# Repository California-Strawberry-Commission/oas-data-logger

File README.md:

# Operator Aid Systems Data Collection

## Objective

A common, fast and reliable method for data collection for Operator Aid Systems, such as bug vac and spray rig.

We continuously gather data from connected sensors, and save it to an SD card. When connected to WiFi, the data is uploaded to a server. We provide a web-based interface to visualize the data.

## Hardware

### v0

The [Adafruit ItsyBitsy ESP32](https://learn.adafruit.com/adafruit-itsybitsy-esp32/overview) was ultimately selected due to its small form factor, relatively large number of GPIO pins, power management, Wi-Fi and Bluetooth capabilities, and I2C connector. We had originally worked with the Sparkfun Thing Plus. However, the ItsyBitsy has a smaller size, extra power management features, and better isolation between the VCC and battery rails. With the Sparkfun Thing Plus, we needed to mod in a better diode onto the board to get USB power detection to work, and found that GPS did not work on I2C (and thus had to use UART).

Relevant features include:

- USB to serial converter chip
- Power regulator
- STEMMA QT I2C connector (which we use for the GPS module)
- Low power (light sleep at 4mA, deep sleep at ~10uA)
- Wi-Fi and Bluetooth
- 20 GPIO pins
- SPI pins (which we use for the MicroSD module)
- User switch
- Small form factor

The GPS module provides support for GPS, GLONASS, GALILEO, and QZSS, providing updates at up to 10 Hz and with both UART and I2C interfaces.

### v1

See https://github.com/California-Strawberry-Commission/oas-data-logger-hardware

## Software

### ESP32

`oas-logger` is a PlatformIO (IDE for embedded systems, based on VSCode) project for the ESP32 to log data from various attached sensors (currently only GPS) using the Arduino API. It depends on `dlflib`, which is used for writing and uploading log data.

### Server

`data-visualizer` is a Next.js app deployed on Vercel for uploading and visualizing OAS data. It depends on `dlflib-js`, which is used for parsing `.dlf` files, and so we use an npm workspace.

See [README.md](software/data-visualizer/README.md).

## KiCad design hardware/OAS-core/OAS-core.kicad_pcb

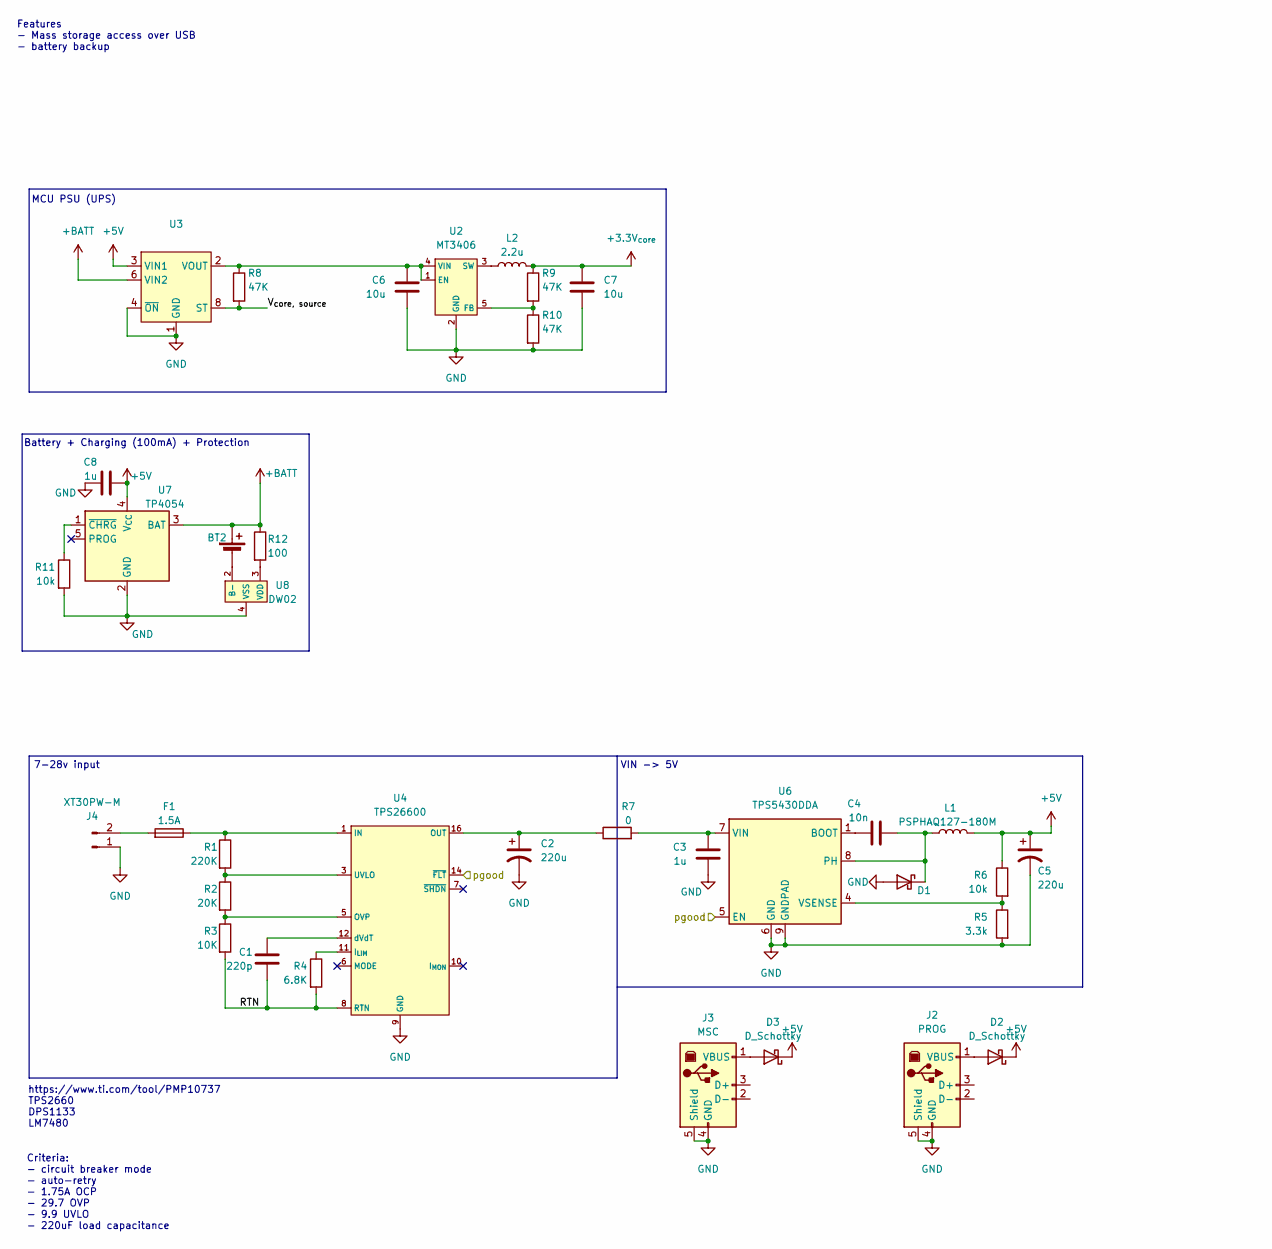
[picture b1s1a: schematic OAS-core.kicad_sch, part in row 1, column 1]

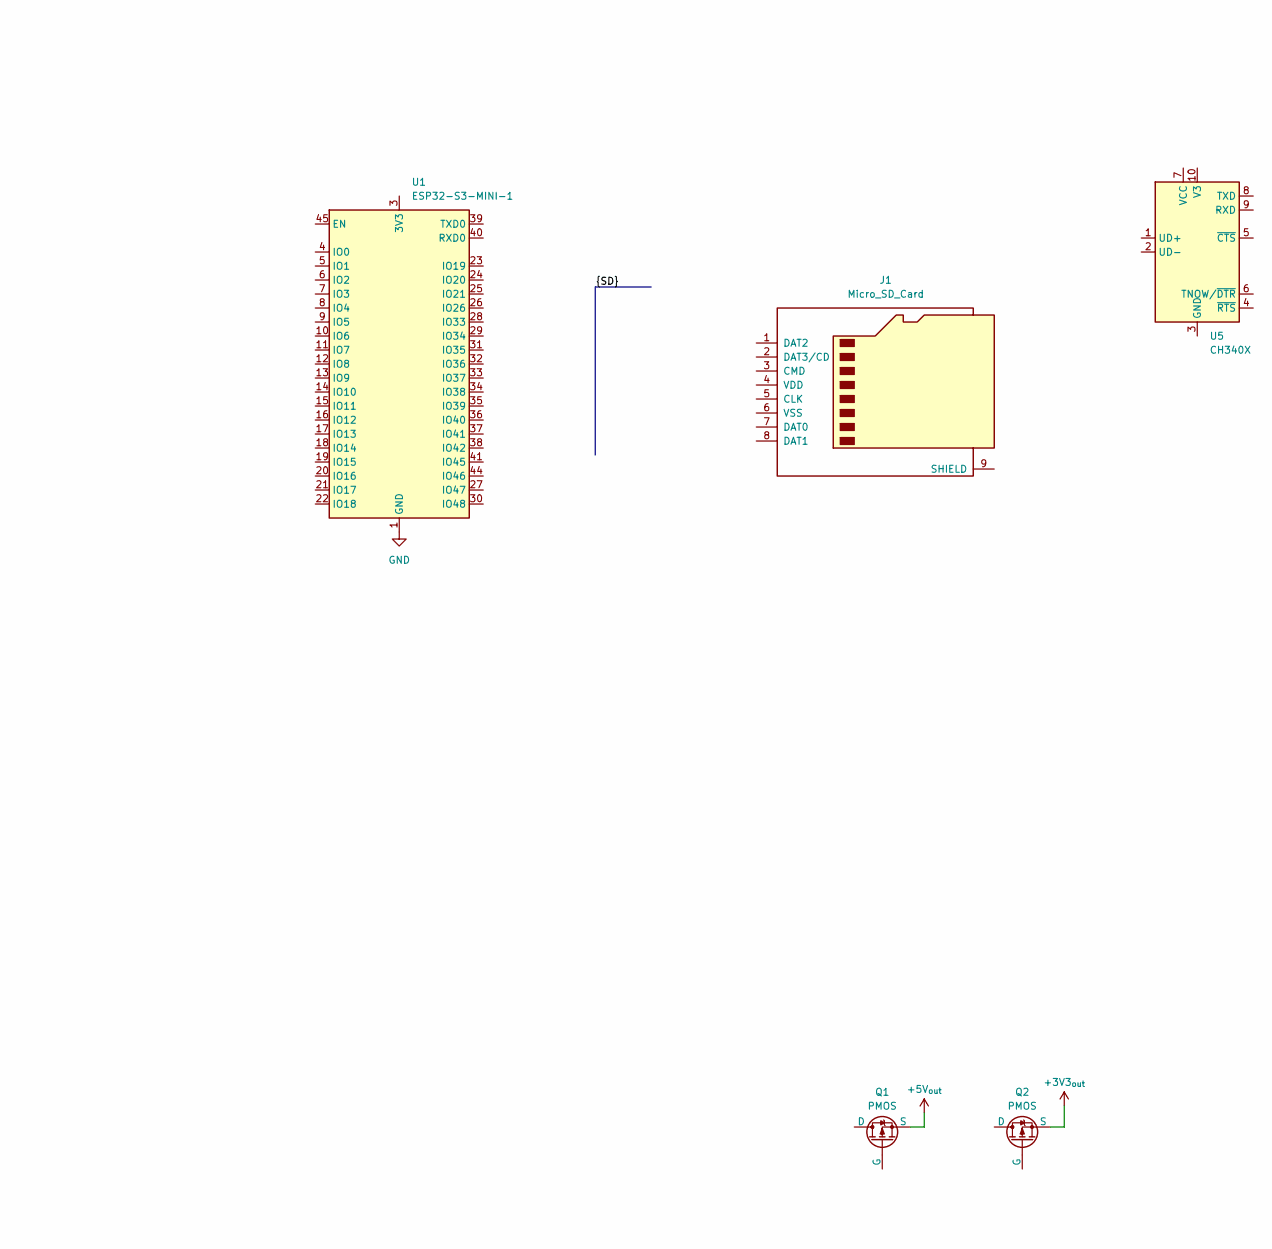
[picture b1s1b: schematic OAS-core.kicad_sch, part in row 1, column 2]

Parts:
BT2: Battery_Cell; JST_PH_B2B-PH-SM4-TB_1x02-1MP_P2.00mm_Vertical
C1: 220p; C_0402_1005Metric
C2: 220u; CP_Elec_8x10.5; LCSC C2983323
C3, C8: 1u; C_0402_1005Metric
C4: 10n; C_0402_1005Metric
C5: 220u; CP_Elec_6.3x5.9; LCSC C2939793
C6, C7: 10u; C_0805_2012Metric; LCSC C15850
D1: D_Schottky; D_SMA; LCSC C7420369
D2, D3: D_Schottky
F1: 1.5A; R_0603_1608Metric; LCSC C2924957
J1: Micro_SD_Card; microSD_HC_Hirose_DM3AT-SF-PEJM5; LCSC C114218
J2: PROG; USB_B_OST_USB-B1HSxx_Horizontal
J3: MSC; USB_B_OST_USB-B1HSxx_Horizontal
J4: XT30PW-M; AMASS_XT30PW-M_1x02_P2.50mm_Horizontal
L1: PSPHAQ127-180M; L_12x12mm_H8mm; LCSC C2983064
L2: 2.2u; L_1008_2520Metric; LCSC C5156791
Q1, Q2: PMOS
R1: 220K; R_0402_1005Metric
R2: 20K; R_0402_1005Metric
R3: 10K; R_0402_1005Metric
R4: 6.8K; R_0402_1005Metric
R5: 3.3k; R_0402_1005Metric; LCSC C25890
R6, R11: 10k; R_0402_1005Metric
R7: 0; R_0402_1005Metric
R8, R9, R10: 47K; R_0402_1005Metric
R12: 100; R_0402_1005Metric
U1: ESP32-S3-MINI-1; ESP32-S2-MINI-1
U2: MT3406; SOT-23-5; LCSC C89358
U3: LM66200; SOT-583-8
U4: TPS26600; HTSSOP-16-1EP_4.4x5mm_P0.65mm_EP3.4x5mm_Mask2.46x2.31mm_The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
U5: CH340X; MSOP-10_3x3mm_P0.5mm
U6: TPS5430DDA; TI_SO-PowerPAD-8_ThermalVias; LCSC C9864
U7: TP4054; TSOT-23-5; LCSC C32574
U8: DW02; SOT-23-5; LCSC C7420470

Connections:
+3.3V_{core}: C7.1, L2.2, R9.1
+5V: C5.1, C8.1, D2.1 (K), D3.1 (K), L1.2, R6.1, U3.3 (VIN1), U7.4 (V_{CC})
+BATT: BT2.1 (+), R12.1, U3.6 (VIN2), U7.3 (BAT)
/RTN: C1.2, R3.2, R4.2, U4.8 (RTN), U4.17 (PAD)
/V_{core, source}: R8.2, U3.8 (ST)
/pgood: U4.14 (~FLT), U6.5 (EN)
GND: C2.2, C3.2, C5.2, C6.2, C7.2, C8.2, D1.2 (A), J2.4 (GND), J2.5 (Shield), J3.4 (GND), J3.5 (Shield), J4.1, R5.2, R10.2, R11.2, U1.1 (GND), U1.2 (GND), U1.42 (GND), U1.43 (GND), U1.46 (GND), U1.47 (GND), U1.48 (GND), U1.49 (GND), U1.50 (GND), U1.51 (GND), U1.52 (GND), U1.53 (GND), U1.54 (GND), U1.55 (GND), U1.56 (GND), U1.57 (GND), U1.58 (GND), U1.59 (GND), U1.60 (GND), U1.61 (GND), U1.62 (GND), U1.63 (GND), U1.64 (GND), U1.65 (GND), U2.2 (GND), U3.1 (GND), U3.4 (~ON), U3.5 (GND), U4.9 (GND), U6.6 (GND), U6.9 (GNDPAD), U7.2 (GND), U8.4 (VSS), U8.5 (VSS)
unnamed: BT2.2 (-), U8.2 (B-)
unnamed: C2.1, R7.1, U4.15 (OUT), U4.16 (OUT)
unnamed: C4.2, D1.1 (K), L1.1, U6.8 (PH)
unnamed: D2.2 (A), J2.1 (VBUS)
unnamed: D3.2 (A), J3.1 (VBUS)
unnamed: F1.1, R1.1, U4.1 (IN), U4.2 (IN)
unnamed: F1.2, J4.2
unnamed: C6.1, R8.1, U2.1 (EN), U2.4 (VIN), U3.2 (VOUT), U3.7 (VOUT)
unnamed: R9.2, R10.1, U2.5 (FB)
unnamed: L2.1, U2.3 (SW)
unnamed: R4.1, U4.11 (I_{LIM})
unnamed: R2.2, R3.1, U4.5 (OVP)
unnamed: R1.2, R2.1, U4.3 (UVLO)
unnamed: C1.1, U4.12 (dVdT)
unnamed: C4.1, U6.1 (BOOT)
unnamed: C3.1, R7.2, U6.7 (VIN)
unnamed: R5.1, R6.2, U6.4 (VSENSE)
unnamed: R11.1, U7.1 (~CHRG)
unnamed: R12.2, U8.3 (VDD)

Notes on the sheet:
VIN -> 5V
Criteria: - circuit breaker mode - auto-retry - 1.75A OCP - 29.7 OVP - 9.9 UVLO - 220uF load capacitance
Battery + Charging (100mA) + Protection
https://www.ti.com/tool/PMP10737 TPS2660 DPS1133 LM7480
7-28v input
MCU PSU (UPS)
Features - Mass storage access over USB - battery backup

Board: 2 copper layers, 37 parts (0 on the bottom side), 24 nets, no tracks yet.

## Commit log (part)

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2026-01-16 [dlflib] s/CSCLogger/DLFLogger
2026-01-20 [oas-logger] Modify app_v0 to check for firmware updates
2026-01-20 [oas-logger] Modify v0 and v1 apps to check for firmware updates (#83)
    * [oas-logger] Modify app_v0 to check for firmware updates
    * [oas-logger] Modify app_v1 to check for firmware updates
2026-01-20 [dlflib] Made necessary changes to decouple dlflib from deviceauth and main.
2026-01-20 Package-lock.json updated
2026-01-20 Revert platformio.ini to main state
2026-01-20 [oas-logger] Changed Serial.println(s) to new logger standard, disabled serial logging until after provisioning state.
2026-01-21 [data-viz] Implement device filter (#85)
2026-01-22 Refactored provision-device.js to be more in line with publish-firmware.mjs
2026-01-22 DeviceAuth revised to use constexpr, a namespace, .c_str() fix, and check hex properly.
2026-01-22 Modified request_signer to use const String& and pass deviceId and secret into the constructor.
2026-01-22 chore: revert platformio.ini changed by VSCode.
2026-01-22 End-to-End Device Authentication & Secure Provisioning (#74)
    * [data-visualizer] API created to facilitate secret encryption for server side.
    * [data-visualizer][prisma] Modify DB schema to support authentication of devices for upload.
    * [data-visualizer] Implement secure device provisioning and HMAC verification JS side.
    * [dlflib] Add authentication headers.
    * [oas-logger] Implement device-side provisioning and authentication.
    * [data-visualizer] Update package.json for serialport and axios under devDependencies.
2026-01-23 [provision] Fix import
2026-01-23 [oas-logger][v1-app] Fix garbled IP log
2026-01-23 [oas-logger] Fix WiFi connection on boot
2026-01-26 [oas-logger] Fix WiFi connection on boot (#93)
    * [oas-logger] Fix WiFi connection on boot
    * [oas-logger] Fixed v1-app compile
2026-01-26 [oas-logger] Add clear log line on boot
2026-01-26 [oas-logger] Tweak order of delay during boot (#97)
2026-01-27 [data-viz] Add provisioned status to Devices list in Admin Portal (#100)
2026-01-27 [data-viz] Make Combobox and selector components controlled and add delete run button to main page
2026-01-28 [oas-logger] Add heap monitor
2026-01-28 [oas-logger] Add heap monitor (#104)
    * [oas-logger] Add heap monitor
    * [oas-logger] Add test flag to app_v0 and app_v1 to log heap usage
2026-01-29 [dlflib] Increased Flusher task stack size.
2026-01-29 [dlflib] Modified comment to address new stack size.
2026-01-30 [ezlog][trivial] Organize static state vars
2026-01-30 [oas-logger] Switch to EzLog
2026-02-02 [data-viz] Add error details to console log for verifyDeviceSignature (#110)
2026-02-02 [oas-logger][ezlog] Add core, task, filename, line, function name to log lines (#111)
2026-02-02 Implement solution to WiFi reconnection never being attempted. (#106)
    * [dlflib] Increased Flusher task stack size.
    * [oas-logger] Implement solution for reconnecting to WiFi when out of range.
    * [dlflib] Modified comment to address new stack size.
    * [oas-logger] Modified Polling Loop comment to be more accurate.
2026-02-04 [data-viz][auth] Add dev bypass for provisioned device auth endpoints
2026-02-04 [data-viz][auth] Add dev bypass for user auth endpoints
2026-02-04 [data-viz] Secure firmware endpoint for provisioned devices only
2026-02-06 [data-viz] Increase dwell radius (#117)
2026-02-11 [data-viz] Revamp UI
2026-02-11 [data-viz] Complete UI revamp (#118)
    * [data-viz] Add top app bar
    * [data-viz] Revamp UI
    * [data-viz] Add logo
    * [data-viz] Responsive UI for mobile
2026-02-11 [data-viz] Loading states in data selector (#120)
2026-02-19 [data-viz] Sync selected timestamp between map and speed chart, and improve performance of rerenders
2026-02-23 [data-viz] Update Prisma to v7 (#125)
2026-02-25 [dlflib] Remove unnecessary type aliases
2026-02-25 [oas-logger][v0] Delete GPS task on sleep
2026-02-27 [dlflib][UploaderComponent] Change connectToEndpoint to just create a unique_ptr of WifiClient to begin with
2026-02-27 [dlflib][UploaderComponent] Close all file handles
2026-03-02 [dlflib][UploaderComponent] Add RetentionMode to options
2026-03-02 [dlflib][UploaderComponent] Avoid heap fragmentation (#127)
    * [dlflib][UploaderComponent] Change connectToEndpoint to just create a unique_ptr of WifiClient to begin with
    * [dlflib][UploaderComponent] Remove unnecessary CRLF from request header
    * [dlflib][UploaderComponent] Close all file handles
    * [dlflib][UploaderComponent] Reuse WiFiClient to avoid heap fragmentation
    * [dlflib] Eliminate usage of String in UploaderComponent
    * [dlflib][UploaderComponent] Add RetentionMode to options
2026-03-02 [dlflib] Eliminate String everywhere except RequestSigner (#128)
    * [dlflib] Eliminate String from AbstractStream and DLFLogger::prune
    * [dlflib] Eliminate String everywhere except RequestSigner
2026-03-03 [PR #129] Requested changes made.
2026-03-03 [data-viz] Implement multiple run visualization
2026-03-05 [data-viz] Add matching color coding to data selector and visualization
2026-03-05 [data-viz] Add comparison limit
2026-03-05 [data-viz] Tweak speed chart tooltip (#132)
2026-03-05 [oas-logger] Remove unused GPS_BAUD_RATE (#133)
2026-03-05 [data-viz] Fix current position marker color (#134)
2026-03-10 [oas-logger] Change DeviceAuth public API to use c-strings and moved logic from main into DeviceAuth that handles provision and reboot sequence. (#136)
    * [oas-logger] Change DeviceAuth public API to use c-strings and moved logic from main into DeviceAuth that handles provision and reboot sequence.
    * [oas-logger][deviceAuth] secretLen to secretBufferLen, comment for minimum size buffer, lastPrint moved to outside loop.
2026-03-10 [oas-logger] Avoid String heap allocs in OtaUpdater
2026-03-11 [data-viz] Make TimeSeriesChart generic (#142)
2026-03-12 [data-viz] Add dwell time chart (#143)
2026-03-13 [data-viz] Sync run selections to URL (#144)
2026-03-18 [data-viz] Remove unnecessary ResponsiveContainer
2026-03-18 [data-viz] When zoomed, adjust Y domain to fit visible data
2026-03-18 [data-viz] Add posthog events
2026-03-18 [data-viz] Integrate product analytics pipeline with PostHog (#149)
    * [data-viz] Integrate PostHog
    * [data-viz] Add posthog events
    * [data-viz] Add posthog identification on page render
2026-03-20 [oas-logger][dlflib] Task sizes decreased to 2560 words based on stack audit. (#150)
2026-03-23 [data-viz] Adjust point downsampling to chart zoom region
2026-03-23 [oas-logger] Enable OTA updates
2026-03-23 [data-viz] Add share button (#155)
2026-03-24 [data-viz] Remove RunData from prisma schema
2026-03-24 [oas-logger] In depth audit of sleep_monitor, increase stack size accordingly (#160)
2026-03-25 [data-viz] Add retries for S3 upload (#164)
2026-03-25 [data-viz] Fix deleting a run to clear run cache (#165)
2026-03-25 [oas-logger] On upload check for any 2XX status
2026-03-25 [data-viz] Fix map recentering when switching between runs
2026-03-30 [dlflib] Move device secret to UploaderComponent Options (#172)
2026-03-30 [oas-logger] Use root CA cert for uploader (#173)
2026-03-30 [oas-logger] Use root CA cert for OTA update (#174)
2026-04-06 [dlflib] Implement chunked uploads (#176)
    * [dlflib] Implement chunked uploads
    * [dlflib][upload] Use chunked upload path for partial uploads
2026-04-07 [oas-logger] Improve sleep button logic to make it feel more responsive (#177)
2026-04-09 [dlflib] Add checks for FreeRTOS resource creation and fix potential stream buffer overrun (#178)
    * [dlflib] Add checks for all FreeRTOS resource creation
    * [dlflib] Fix potential stream buffer overrun when there are many event streams
2026-04-09 [oas-logger] Ensure state machine state is thread safe
2026-04-10 [data-viz] API route param validation
2026-04-10 [data-viz][trivial] Update README example request to reflect valid UUID requirement (#181)
2026-04-13 [data-viz] Extract api route auth logic to a handler wrapper (#182)
2026-04-13 [data-viz] Add unit tests for data-visualizer (#183)
    * [data-viz] Add scaffolding for vitest unit tests
    * [data-viz] Add unit tests for lib
2026-04-15 Add test script to root package.json
2026-04-15 Add test github workflow
2026-04-15 Add Github Action for building firmware (#186)
2026-04-15 [dlflib-js][encoder] Modified comments, moved float implementation to construct_floats.ts.
2026-04-15 Rename test workflow to server
2026-04-15 [dlflib-js][package.json] Add construct-js and ieee754 dependencies.
2026-04-16 [dlflib-js] Clean up config files (#188)
2026-04-17 Bump dependency versions to address security alerts
2026-04-17 [oas-logger] Log WiFi RSSI
2026-04-17 [dlflib-js][construct_float] Comment created acknowledging source code origins.
2026-04-17 [software] Update package-lock.json for npm installs.
2026-04-21 [data-viz] Add map overlay for wifi RSSI (#192)
2026-04-22 [data-viz] Only show wifi rssi overlay if there exists wifi data
2026-04-23 [data-viz] Modify combobox to scroll to the selected element when expanded
2026-04-23 [data-viz] Add run summary
2026-04-24 [data-viz] Move GPS data processing functions into separate functions and add unit tests
2026-04-24 [data-viz] Move GPS data processing functions into separate functions and add unit tests for gps viz (#197)
    * [data-viz] Move GPS data processing functions into separate functions and add unit tests
    * [data-viz] Add unit tests for time-series-chart
2026-04-28 [dlflib-js][dlflib.ts] Removed unused import NullTerminatedStringType.
2026-04-29 [dlflib] Update README
2026-04-29 [dlflib-js][dlflib.ts] Match offset to _____offset, utilize create_parser logic to handle non-primitive in polled_data.
2026-04-30 [dlflib-js][dlflib.ts] Addressed PR comments.
2026-05-04 [dlflib-js][dlflib.ts] Passed size to getEncoderField.
2026-05-07 [data-viz] Fix import in gps-processing.test.ts
2026-05-08 [data-viz] Implement GPS data visualization for Day view mode
2026-05-08 [dlflib-js] Rename types, variables, methods to improve clarity and consistency
2026-05-08 New commit
2026-05-08 [dlflib-js] Additional typing (#203)
2026-05-11 [data-viz] Add ability to select and visualize data by session (#206)
    * [data-viz] Swap Run and Day selector positions
    * [data-viz] Add ability to select and visualize data by session
2026-05-11 [data-viz] For map and charts in session view, ensure we don't connect points across different runs (#207)
2026-05-11 [data-viz] Add missing dwellMinsSeries dep when memoizing sessionSummaries
2026-05-11 [data-viz] Fix session view URL handling
2026-05-11 [oas-logger][DeviceAuth] Added provisioning helpers for duplicated logic, added functionality for pulling secret from already provisioned device, moved unnecessarily public functions to private.
2026-05-11 [oas-logger][DeviceAuth] Match variable used to parameter name after changing for readability.
2026-05-12 [oas-logger] Attempt wifi reconnect during RUNNING state and turn on partial uploads (#214)
2026-05-12 [data-viz] Add Live indicator to summary cards (#215)
    * [data-viz] Fix active indicator when selecting a session
    * [data-viz] Add Live indicator to summary cards
2026-05-14 Trialed a few approaches for reliability, picked cleanest one which aligned with your suggestion.
2026-05-14 [oas-logger][app_v1][rev2] Pin changes and LED for rev2.
2026-06-01 [dlflib] Fix bug where calling LogFile::flush will corrupt the logfile
2026-06-01 Hard migration to new board specs, Genki will run v0.
2026-06-02 [dlflib][partial uploads] Don't finalize on chunk upload (#220)
    * [dlflib] Add chunkUploadTimeoutMs to options
    * [dlflib][partial uploads] Don't finalize on chunk upload
2026-06-02 [data-viz] When visualizing active run or session, automatically refetch data (#222)
2026-06-02 [oas-logger][rev2] Pinouts changed for Rev2 board and associated LED changes implemented (#216)
2026-06-03 [data-viz] Periodically merge chunks for active runs using partial uploads (#224)
    * [data-viz] Periodically merge chunks for active runs using partial uploads
    * [data-viz] Remove from finalize request body
2026-06-16 [data-viz] Update deps for dependabot (#225)
2026-06-29 [data-viz][poi] Add colors to POIs
2026-06-29 [data-viz][poi] Clicking on a POI in the panel centers map on that point
2026-06-29 [data-viz][poi] Wire up posthog events
2026-06-30 [data-viz] Integrate Nimbo map tiles (#230)
